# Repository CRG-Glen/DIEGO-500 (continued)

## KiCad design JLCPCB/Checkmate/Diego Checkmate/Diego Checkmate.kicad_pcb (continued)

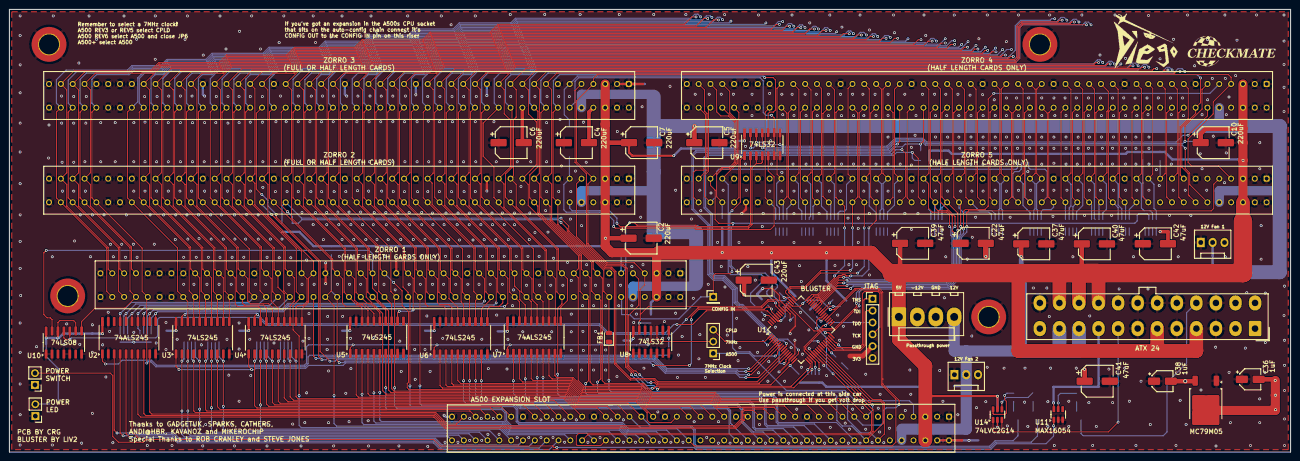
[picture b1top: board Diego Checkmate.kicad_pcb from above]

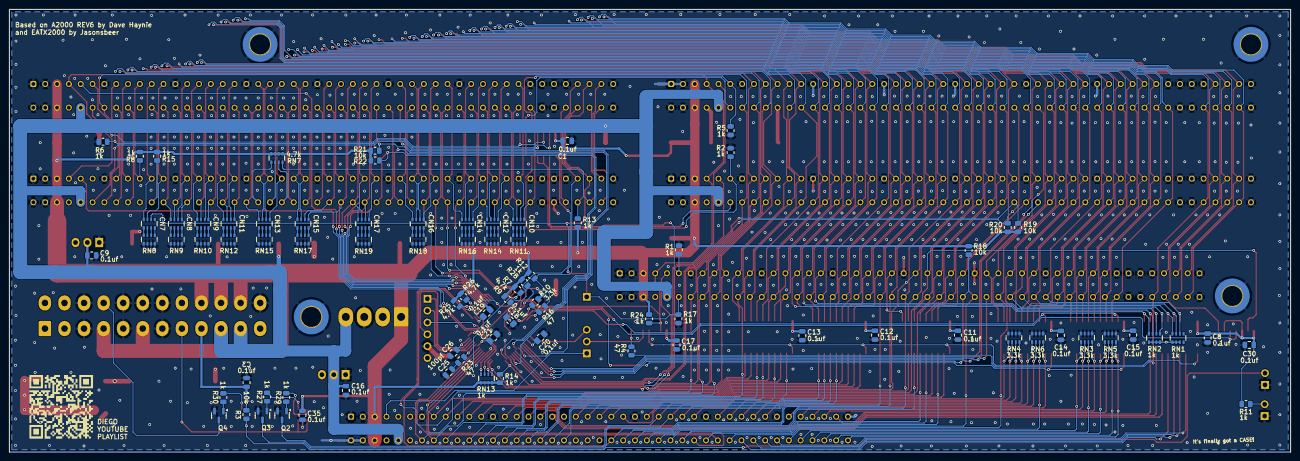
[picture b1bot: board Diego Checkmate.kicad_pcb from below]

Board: 4 copper layers, 275.0 x 95.0 mm, 130 parts (82 on the bottom side), 223 nets.

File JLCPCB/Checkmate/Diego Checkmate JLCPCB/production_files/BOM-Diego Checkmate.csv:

Comment,Designator,Footprint,LCSC,Quantity
0.1uf,"C1,C11,C12,C13,C14,C15,C16,C17,C18,C19,C20,C21,C3,C30,C35,C8,C9",C_0805_2012Metric,C49678,17
1000pf,"CN10,CN11,CN12,CN13,CN14,CN15,CN16,CN17,CN7,CN8,CN9",R_Array_Convex_4x0603,C541606,11
100pf,"C25,C26",C_0805_2012Metric,C1790,2
10k,"R18,R19,R20,R21,R22,R3",R_0805_2012Metric,C17414,6
1k,"R1,R11,R12,R13,R14,R15,R17,R2,R24,R27,R28,R29,R30,R5,R6,R8",R_0805_2012Metric,C17513,16
1k,"RN1,RN10,RN11,RN12,RN13,RN14,RN15,RN16,RN17,RN18,RN19,RN2,RN8,RN9",R_Array_Convex_4x0603,C20197,14
1uF,"C36,C38",CP_Elec_4x5.4,C3348,2
220uF,"C10,C2,C4,C43,C5,C6,C7",CP_Elec_6.3x7.7,C278407,7
3.3k,R10,R_0805_2012Metric,C26010,1
3.3k,"RN3,RN4,RN5,RN6",R_Array_Convex_4x0603,C425215,4
4.7k,"R25,R26,R7,R9",R_0805_2012Metric,C17673,4
4.7k,RN7,R_Array_Convex_4x0603,C66697,1
47,"R16,R23,R4",R_0805_2012Metric,C17714,3
47uF,"C22,C37,C39,C40,C41,C42",CP_Elec_6.3x7.7,C336249,6
74ALS245,"U2,U7",SO-20_5.3x12.6mm_P1.27mm,C2675885,2
74LS08,U10,SO-14_3.9x8.65mm_P1.27mm,C6802,1
74LS245,"U3,U4,U5,U6",SO-20_5.3x12.6mm_P1.27mm,C7753,4
74LS32,"U8,U9",SO-14_3.9x8.65mm_P1.27mm,C116812,2
74LVC2G14,U14,SOT-23-6,C12401,1
A500 side car,CN1,Samtec_HLE-150-02-xx-DV-TE_2x43_P2.54mm_Horizontal,C5173317,1
BLUSTER,U1,TQFP-64_10x10mm_P0.5mm,C90569,1
FerriteBead_Small,FB1,D_0805_2012Metric,C1015,1
MAX16054,U11,SOT-23-6,C79401,1
MC79M05,U15,TO-252-2,C126401,1
S8050,"Q2,Q3,Q4",SOT-23,C2146,3
Zorro 1,CN2,Samtec_HLE-150-02-xx-DV-TE_2x50_P2.54mm_Horizontal,C5173320,1
Zorro 2,CN3,Samtec_HLE-150-02-xx-DV-TE_2x50_P2.54mm_Horizontal,C5173320,1
Zorro 3,CN4,Samtec_HLE-150-02-xx-DV-TE_2x50_P2.54mm_Horizontal,C5173320,1
Zorro 4,CN5,Samtec_HLE-150-02-xx-DV-TE_2x50_P2.54mm_Horizontal,C5173320,1
Zorro 5,CN6,Samtec_HLE-150-02-xx-DV-TE_2x50_P2.54mm_Horizontal,C5173320,1
Power LED,J4,PinHeader_1x02_P2.54mm_Vertical,,1
Conn_01x04,J2,Molex_KK-396_A-41791-0004_1x04_P3.96mm_Vertical,,1
Fan 2,M2,FanPinHeader_1x03_P2.54mm_Vertical,,1
Conn_01x02_Pin,J3,PinHeader_1x02_P2.54mm_Vertical,,1
ATX-24,J10,Molex_Mini-Fit_Jr_5566-24A_2x12_P4.20mm_Vertical,,1
Buster,J7,PinHeader_1x06_P2.54mm_Vertical,,1
Conn_01x03_Pin,J1,PinHeader_1x03_P2.54mm_Vertical,,1
Conn_01x01_Pin,J9,PinHeader_1x01_P2.54mm_Vertical,,1
Fan 1,M1,FanPinHeader_1x03_P2.54mm_Vertical,,1
